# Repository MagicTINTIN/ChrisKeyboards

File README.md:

# ChrisKeyboards

> I couldn’t find the keyboard I wanted, so I built it.

---
Unable to find an USB chiclet keyboard as we have on laptop (and with a reasonable price), I decided to create mine.\
We can recover keyboard from an old laptop or buy a spare one (the one I chose is exactly the same that I have on my laptop, with backlight so it cost me 36 euros, but you can easily find cheaper ones).

## Components
- spare laptop keyboard (here with a 30 pins 0.8mm FPC ribbon)
- ESP32-S3 (we need about 30 IO pins...)
- 2 FPC connectors: 30 pins 0.8mm `for keys`, 6 pins (couldn't find 4 pins that meet requirements) 1mm `for backlight`
- Dupont cables while we don't have PCB
- (optional) speaker

## Road map
- [x] get components
- [x] assemble everything on a breadboard
- [x] program the esp32
- [x] testing the prototype in real conditions
- [x] implement missing features
- [ ] design PCB
- [ ] 3D model the case
- [ ] get last components
- [ ] print the case
- [ ] assemble the final keyboard

## Project pictures

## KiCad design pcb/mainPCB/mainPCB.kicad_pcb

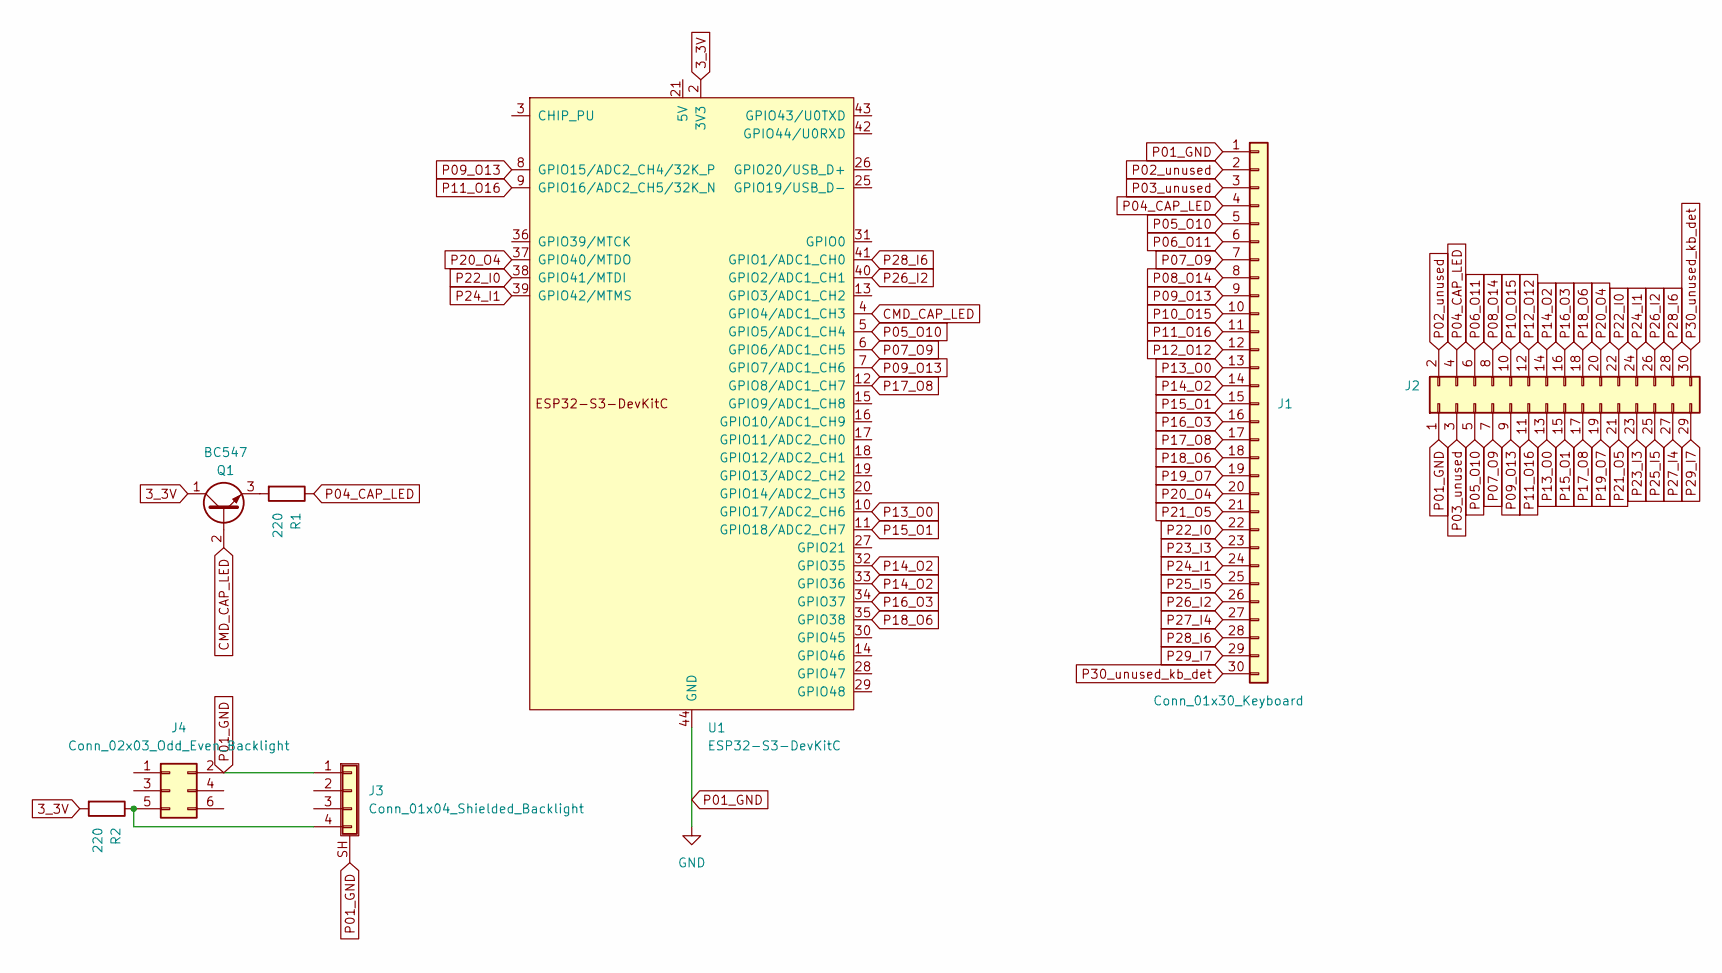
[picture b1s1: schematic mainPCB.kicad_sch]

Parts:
J1: Conn_01x30_Keyboard; FPC_30_Dell_0.8mm_no0
J2: Conn_02x15_Counter_Clockwise; PinHeader_2x15_P2.54mm_Vertical
J3: Conn_01x04_Shielded_Backlight; FPC_4_Dell_1mm_with0
J4: Conn_02x03_Odd_Even_Backlight; PinHeader_2x03_P2.00mm_Vertical
Q1: BC547; TO-92_Inline
R1, R2: 220; R_Axial_DIN0207_L6.3mm_D2.5mm_P10.16mm_Horizontal
U1: ESP32-S3-DevKitC

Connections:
3_3V: Q1.1 (C), R2.2, U1.1 (3V3), U1.2 (3V3)
CMD_CAP_LED: Q1.2 (B), U1.4 (GPIO4/ADC1_CH3)
unnamed: J3.4, J4.5, R2.1
unnamed: Q1.3 (E), R1.2
P01_GND: J1.1, J2.1, J3.1, J3.SH (Shield), J4.2, U1.22 (GND), U1.23 (GND), U1.24 (GND), U1.44 (GND)
P02_unused: J1.2, J2.2
P03_unused: J1.3, J2.3
P04_CAP_LED: J1.4, J2.4, R1.1
P05_O10: J1.5, J2.5, U1.5 (GPIO5/ADC1_CH4)
P06_O11: J1.6, J2.6
P07_O9: J1.7, J2.7, U1.6 (GPIO6/ADC1_CH5)
P08_O14: J1.8, J2.8
P09_O13: J1.9, J2.9, U1.7 (GPIO7/ADC1_CH6), U1.8 (GPIO15/ADC2_CH4/32K_P)
P10_O15: J1.10, J2.10
P11_O16: J1.11, J2.11, U1.9 (GPIO16/ADC2_CH5/32K_N)
P12_O12: J1.12, J2.12
P13_O0: J1.13, J2.13, U1.10 (GPIO17/ADC2_CH6)
P14_O2: J1.14, J2.14, U1.32 (GPIO35), U1.33 (GPIO36)
P15_O1: J1.15, J2.15, U1.11 (GPIO18/ADC2_CH7)
P16_O3: J1.16, J2.16, U1.34 (GPIO37)
P17_O8: J1.17, J2.17, U1.12 (GPIO8/ADC1_CH7)
P18_O6: J1.18, J2.18, U1.35 (GPIO38)
P19_O7: J1.19, J2.19
P20_O4: J1.20, J2.20, U1.37 (GPIO40/MTDO)
P21_O5: J1.21, J2.21
P22_I0: J1.22, J2.22, U1.38 (GPIO41/MTDI)
P23_I3: J1.23, J2.23
P24_I1: J1.24, J2.24, U1.39 (GPIO42/MTMS)
P25_I5: J1.25, J2.25
P26_I2: J1.26, J2.26, U1.40 (GPIO2/ADC1_CH1)
P27_I4: J1.27, J2.27
P28_I6: J1.28, J2.28, U1.41 (GPIO1/ADC1_CH0)
P29_I7: J1.29, J2.29
P30_unused_kb_det: J1.30, J2.30

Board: 2 copper layers, 8 parts (0 on the bottom side), 34 nets, no tracks yet.

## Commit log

2025-04-14 feat: compile script
2025-04-14 chore: gitignore & sdk default config
2025-04-14 feat: compile step range
2025-04-14 chore: CMake & gitignore + more sdk defaults
2025-04-14 doc: add dependency command
2025-04-14 chore: usefull commands
2025-04-14 feat: doc example
2025-04-14 fix: uploading stage
2025-04-14 fix: vscode ferme sa gueule
2025-04-14 feat: now appears as ChrisT1 Clavier
2025-04-15 feat: debug monitor
2025-04-15 fix: more vscode dependencies + compd option
2025-04-15 chore: moving to c++
2025-04-15 test: some tests with keycodes
2025-04-15 doc: kbd dell
2025-04-15 test: attempt to make an oscillo
2025-04-15 doc: wiring pin/gpio
2025-04-15 doc: dell datasheet
2025-04-16 fix: rx tx wires conflict
2025-04-16 feat: test rows/columns detection
2025-04-16 test: are there diods ?
2025-04-16 ressources with arduino pdc
2025-04-16 feat: back/skip buttons
2025-04-16 feat: matrix generator
2025-04-16 doc: matrix
2025-04-16 feat: filled matrix in .cc + fn key
2025-04-16 test: what is europe key ?
2025-04-16 chore: update keys registration
2025-04-17 feat: key registration
2025-04-17 feat: mod key registration
2025-04-17 feat: sending keys (apparently not the right ones)
    en plus il écrit tout seul commme un con visiblement, c'est super
2025-04-17 fix: gpios were also used by usb... + debug stuff
2025-04-17 fix: sending modifiers as keys
2025-04-18 feat: determination of fnMatrix
2025-04-18 feat: function key + other hids
2025-04-18 feat: fnlock
2025-04-19 chore: preparing usage
2025-04-19 chore: try to add usage consumer
2025-04-19 rijfozpkpef
2025-04-19 MAIS PUTAIN !!!
2025-04-19 feat: OMG ÇA MARCHE ENFIN !
2025-04-20 bug: makes grub crash :/
    RAAAAAAAAAAAAAAAAAAAAAAAAAAAAAA
2025-04-20 fix: keyboard working in grub again
2025-04-20 euh: rien ne marche, merde !
2025-04-20 chore: setup pour que ça marche
2025-04-21 chore: c'est juste de la grande merde
2025-04-21 feat: trou du cul bien sûr il faut changer la conf !
2025-04-21 feat: all keys are now working ! even brightness ones
2025-04-22 feat: adding 3d model directory
2025-04-23 chore: trying to use plane
2025-04-23 feat: bevel key params
2025-04-23 feat: split on spaces
2025-04-23 feat: key arrays
2025-04-23 doc: keyboard dimensions
2025-04-23 doc: measuring keys
2025-04-23 doc: adding better reference (800mm focal) and measures
2025-04-23 doc: adding all keyboard (except num pad) measurements
2025-04-23 doc: all keys are measured + "Over" 3d model
2025-05-01 fix: </> keys not working (EU 2)
    Fixes #3
2025-05-03 feat: buzzer
2025-05-03 fix: not registering first already pressed key
2025-05-03 feat: bipping on each key + multithreading
2025-05-03 feat: frequency changing depending on keys
2025-05-03 feat: now uses frequencies
2025-05-26 feat: adding base kicad pcb ( + esp lib)
2025-05-26 wip pccb
2025-05-26 ignoring kicad backups in repo
2025-05-29 chore: another way to scan keyboard
2025-05-29 feat: adding a raw keys array
2025-05-29 chore: partial fix with a blocking algorithm #5 (remember previous keys)
2025-05-30 wip: dropping 2/4 keys (#5)
2025-05-30 chore: improvement (less ghosts, but still some at press) #5
    do not watch for the whole rectangle but just for one of the 4 triangles of each rectangle
    ←↑↓ do not produces 0 now, but ←↑→↓ still produces a 1
    zed still produces a s sometimes at press
2025-05-30 doc: how to prevent ghost keys on diodeless (#5)
2025-05-30 chore: almost every 3-key ghost removed (#5)
2025-05-30 doc: fix schema
2025-05-30 wip: filtered raw buffer (#5) no visible improvement
2025-05-30 fix: reusing open drain in/out in each scan
    Fixes #5
    Closes #6
2025-05-30 doc: documenting ghost key blocking algo
2025-06-08 feat: adding 40pin connector
2025-06-08 feat: 30pins connector
2025-06-08 oskur, cette personne fait sûrement n'imp mais ne s'en aperçois même pas (découvrez son histoire)
2025-06-08 doc: esp32 doc
2025-06-08 feat: scroll lock key (nobody asked for it)
2025-06-08 feat: caps lock LED yay
2025-06-08 pcb: hmmm yes that's better with labels
2025-06-15 doc: adding resistor information
2025-06-15 wip: starting pcb wiring
2025-06-15 wip: starting no crossing cable
2025-06-16 chore: update config to enable bluetooth (BLE)
2025-06-22 feat: bicolor over 3d model version
2025-06-22 feat: spliting model for 3D printing
2025-06-24 feat: adding ble lib example from esp-idf
2025-06-24 build: compiling including the ble lib
2025-06-24 feat: bluetooth device
2025-06-24 fix: only disable key to ble only if necessary
2025-06-24 feat: caps lock indicator information on bluetooth
2025-06-24 feat: bluetooth transmission of normal keys
2025-06-24 wip: bluetooth hid consumers
2025-06-24 wip: adding some debug/doc
2025-06-28 wip: temporary redisabling bluetooth
2025-08-03 chore: switching to C (as it is C)
2025-09-26 doc: short description of the project
2025-10-08 style: adding logo
2026-02-22 chore: adding backlight connectors
2026-02-28 feat: adding NPN for caps led
2026-03-01 chore: more cables
2026-05-01 fix: consumer empty buffer for key release
    Closes #11
2026-05-01 chore: esp idf migrated 5.1->6
    Closes #12
2026-05-01 feat: fn arrows to page up/down, begin/end
    Closes #8
2026-05-01 feat: mykey registration state -> solve "random" fnLock
    Closes #4
2026-05-03 feat: declaring tusb max hid itf=4
2026-05-03 feat: storing configuration in nvs
2026-05-03 feat: indicating gamepad conf at startup using task on caps lock led
2026-05-03 feat: gamepad keys definition and pre-registration check
2026-05-04 chore: adding gamepad internal state
2026-05-04 feat: sending left joystick of the two gamepads
2026-05-05 feat: interface settings != enabled gamepad
    Closes #16
    No more reboot/cycling over configurations needed
2026-05-05 chore: mapping all gamepad keys + dpad matrix
2026-05-05 feat: adding dpads
2026-05-06 fix: 2nd dpad never sending data
2026-05-06 feat: binding all other gamepad keys
2026-05-17 refactor: fn keys have their own pressed layout checks
2026-05-17 feat: control the keyboard's sound
    Closes #14
